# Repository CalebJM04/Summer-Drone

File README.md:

# Summer-Drone
Summer Drone project

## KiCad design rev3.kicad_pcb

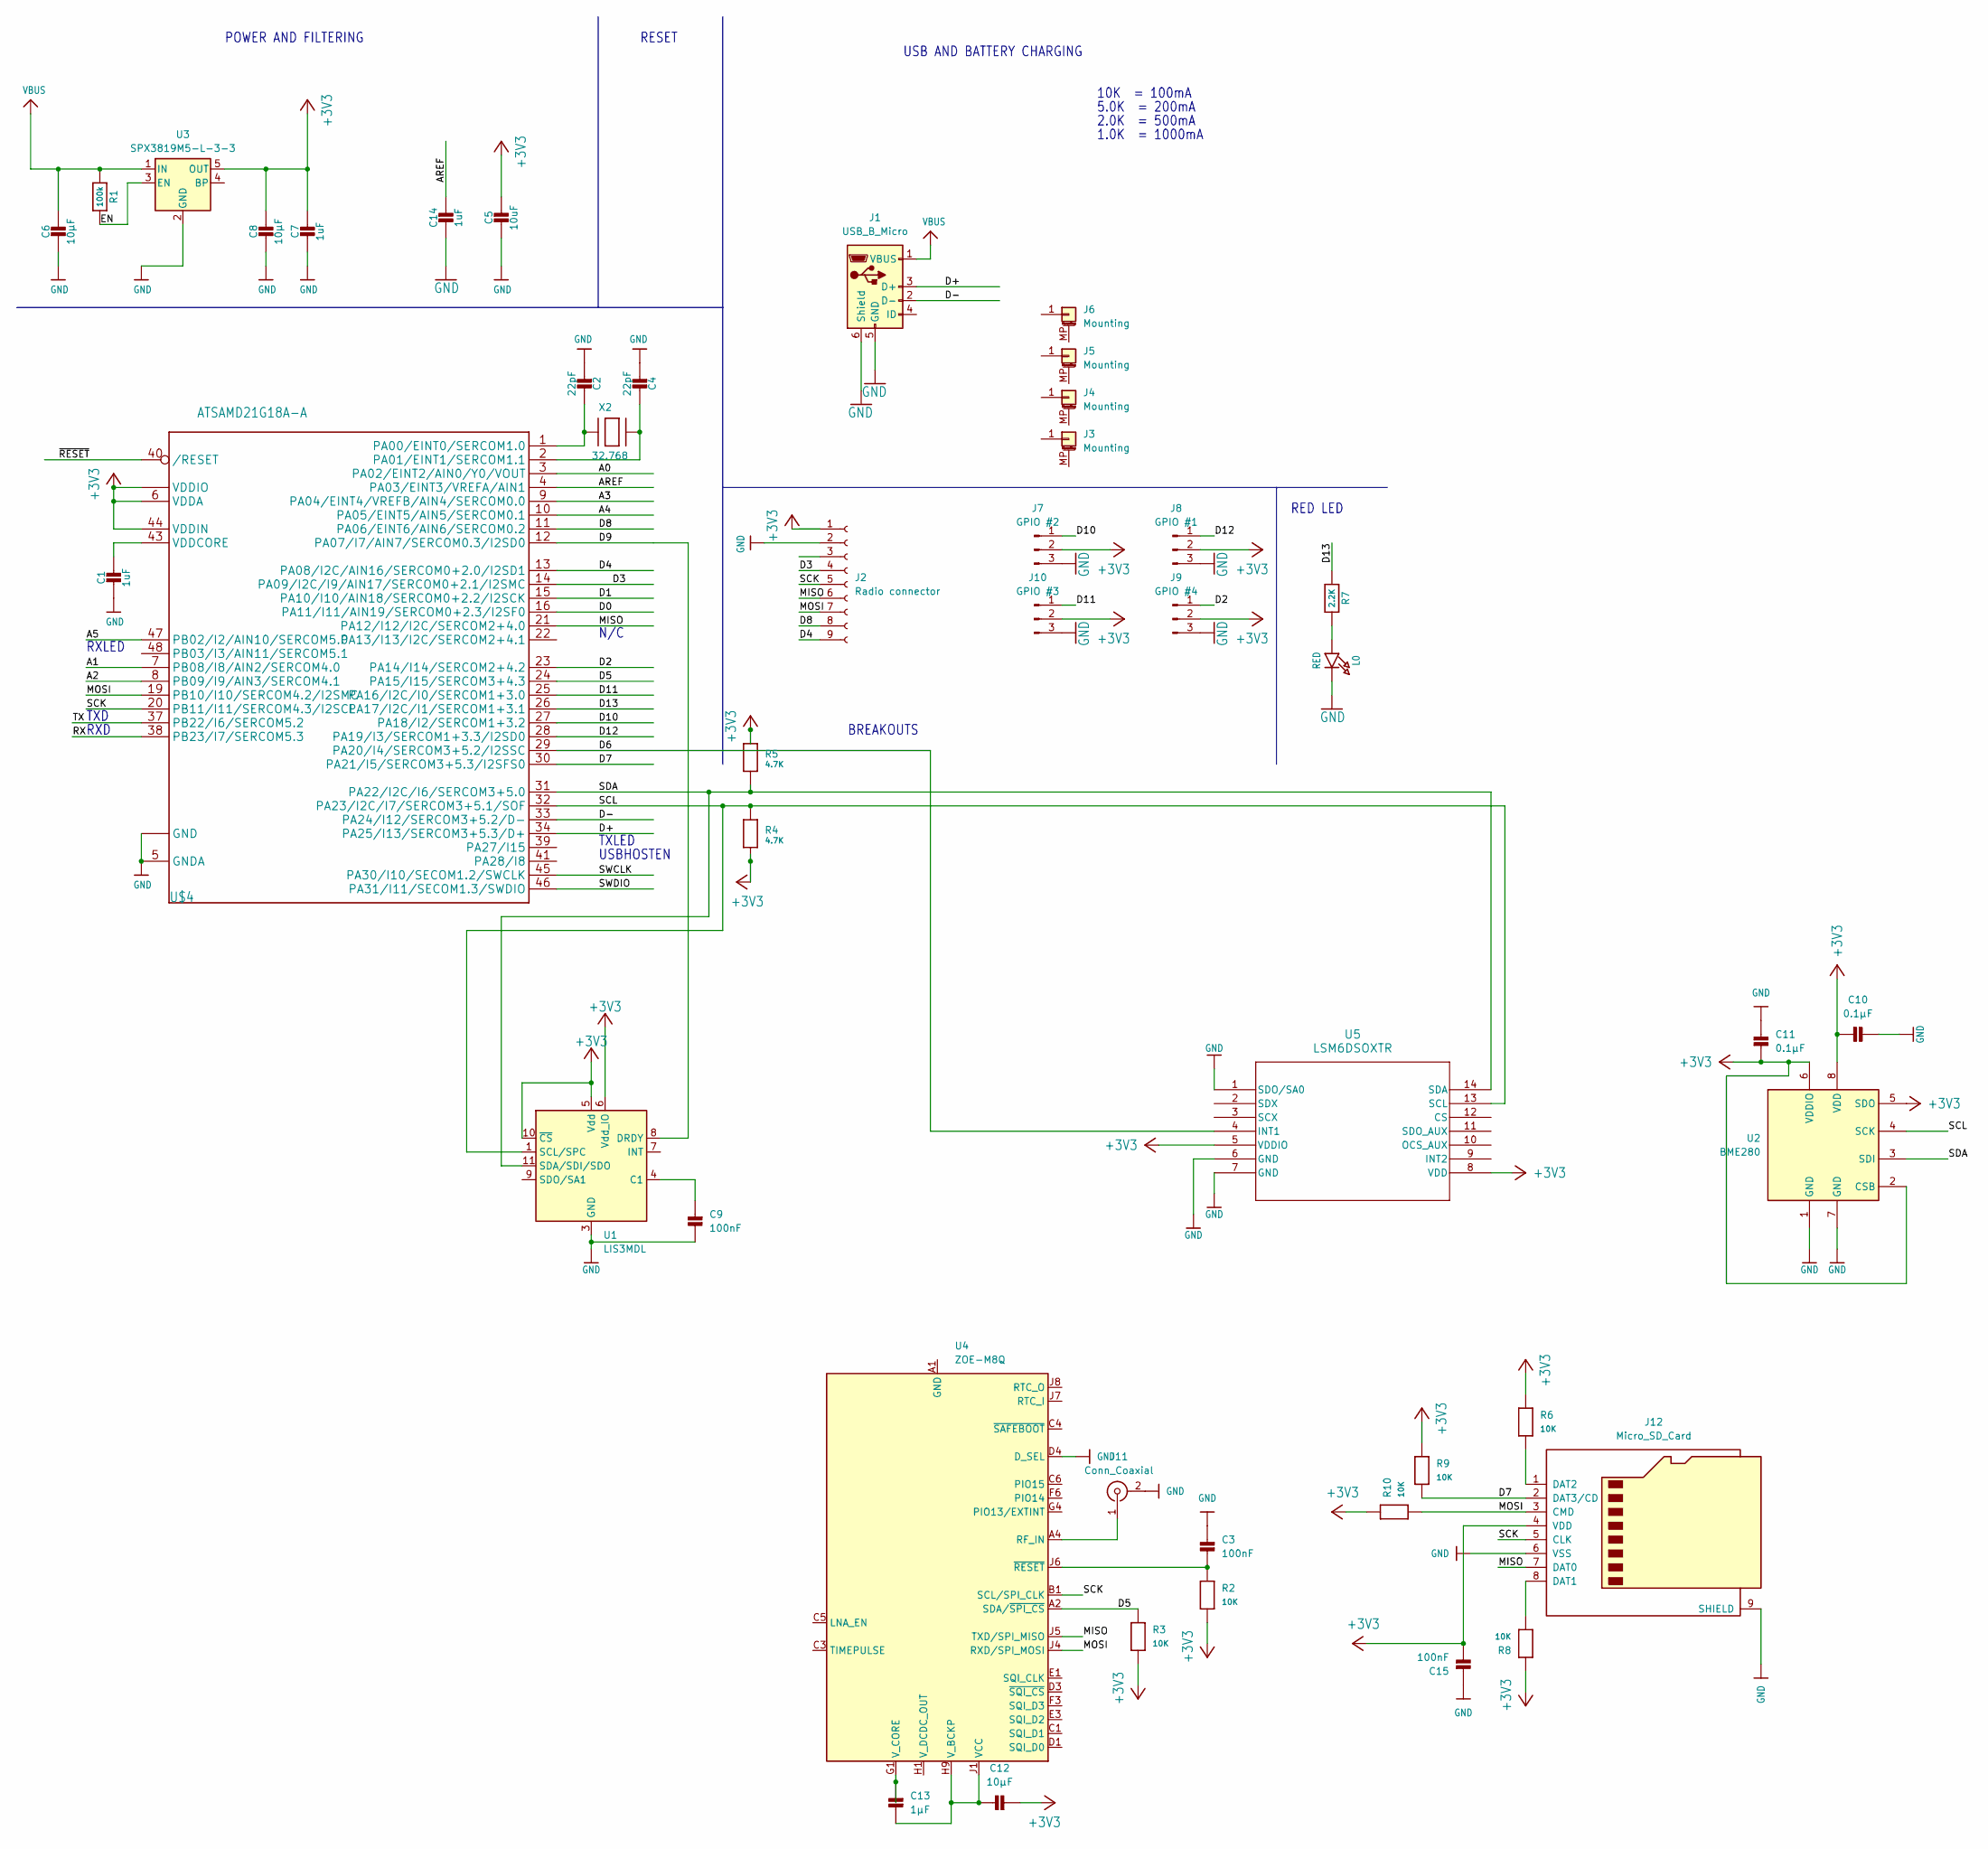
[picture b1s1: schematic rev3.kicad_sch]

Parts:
C1, C7, C14: 1uF; C_0805_2012Metric
C2, C4: 22pF; C_0805_2012Metric
C3, C9, C15: 100nF; C_0805_2012Metric
C5: 10uF; C_0805_2012Metric
C6, C8, C12: 10µF; C_0805_2012Metric
C10, C11: 0.1µF; C_0805_2012Metric
C13: 1µF; C_0805_2012Metric
J1: USB_B_Micro; USB_Micro-B_Molex-105017-0001
J2: Radio connector; PinSocket_1x09_P2.54mm_Vertical
J3, J4, J5, J6: Mounting; MountingHole_2.2mm_M2
J7: GPIO #2; PinHeader_1x04_P2.54mm_Vertical
J8: GPIO #1; PinHeader_1x04_P2.54mm_Vertical
J9: GPIO #4; PinHeader_1x04_P2.54mm_Vertical
J10: GPIO #3; PinHeader_1x04_P2.54mm_Vertical
J11: Conn_Coaxial; U.FL_Molex_MCRF_73412-0110_Vertical
J12: Micro_SD_Card; microSD_HC_Hirose_DM3AT-SF-PEJM5
L0: RED; LED_0805_2012Metric
R1: 100k; R_0201_0603Metric
R2, R3, R6, R8, R9, R10: 10K; R_0201_0603Metric
R4, R5: 4.7K; R_0201_0603Metric
R7: 2.2K; R_0201_0603Metric
U1: LIS3MDL; LGA-12_2x2mm_P0.5mm
U2: BME280; Bosch_LGA-8_2.5x2.5mm_P0.65mm_ClockwisePinNumbering
U3: SPX3819M5-L-3-3; SOT-23-5
U4: ZOE-M8Q; ublox_ZOE_M8
U5: LSM6DSOXTR; LGA-14L_STM
U$4: ATSAMD21G18A-A; TQFP-48_7x7mm_P0.5mm
X2: 32.768; Crystal_SMD_3215-2Pin_3.2x1.5mm

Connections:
+3V3: C5.1, C7.1, C8.1, C10.2, C11.2, C12.2, C15.1, J2.1, J7.2, J8.2, J9.2, J10.2, J12.4 (VDD), R2.1, R3.1, R4.1, R5.2, R6.2, R8.2, R9.2, R10.2, U1.5 (Vdd), U1.6 (Vdd_IO), U1.10 (~CS), U2.2 (CSB), U2.5 (SDO), U2.6 (VDDIO), U2.8 (VDD), U3.5 (OUT), U5.5 (VDDIO), U5.8 (VDD), U$4.6 (VDDA), U$4.17 (VDDIO), U$4.36 (VDDIO), U$4.44 (VDDIN)
/A0: U$4.3 (PA02/EINT2/AIN0/Y0/VOUT)
/A1: U$4.7 (PB08/I8/AIN2/SERCOM4.0)
/A2: U$4.8 (PB09/I9/AIN3/SERCOM4.1)
/A3: U$4.9 (PA04/EINT4/VREFB/AIN4/SERCOM0.0)
/A4: U$4.10 (PA05/EINT5/AIN5/SERCOM0.1)
/A5: U$4.47 (PB02/I2/AIN10/SERCOM5.0)
/AREF: C14.1, U$4.4 (PA03/EINT3/VREFA/AIN1)
/D0: U$4.16 (PA11/I11/AIN19/SERCOM0+2.3/I2SF0)
/D1: U$4.15 (PA10/I10/AIN18/SERCOM0+2.2/I2SCK)
/D2: J9.1, U$4.23 (PA14/I14/SERCOM2+4.2)
/D3: J2.4, U$4.14 (PA09/I2C/I9/AIN17/SERCOM0+2.1/I2SMC)
/D4: J2.9, U$4.13 (PA08/I2C/AIN16/SERCOM0+2.0/I2SD1)
/D5: R3.2, U4.A2 (SDA/~SPI_CS), U$4.24 (PA15/I15/SERCOM3+4.3)
/D6: U5.4 (INT1), U$4.29 (PA20/I4/SERCOM3+5.2/I2SSC)
/D7: J12.2 (DAT3/CD), R9.1, U$4.30 (PA21/I5/SERCOM3+5.3/I2SFS0)
/D8: J2.8, U$4.11 (PA06/EINT6/AIN6/SERCOM0.2)
/D9: U1.8 (DRDY), U$4.12 (PA07/I7/AIN7/SERCOM0.3/I2SD0)
/D10: J7.1, U$4.27 (PA18/I2/SERCOM1+3.2)
/D11: J10.1, U$4.25 (PA16/I2C/I0/SERCOM1+3.0)
/D12: J8.1, U$4.28 (PA19/I3/SERCOM1+3.3/I2SD0)
/D13: R7.1, U$4.26 (PA17/I2C/I1/SERCOM1+3.1)
/D+: J1.3 (D+), U$4.34 (PA25/I13/SERCOM3+5.3/D+)
/D-: J1.2 (D-), U$4.33 (PA24/I12/SERCOM3+5.2/D-)
/EN: R1.2, U3.3 (EN)
/MISO: J2.6, J12.7 (DAT0), U4.J5 (TXD/SPI_MISO), U$4.21 (PA12/I12/I2C/SERCOM2+4.0)
/MOSI: J2.7, J12.3 (CMD), R10.1, U4.J4 (RXD/SPI_MOSI), U$4.19 (PB10/I10/SERCOM4.2/I2SMC)
/RX: U$4.38 (PB23/I7/SERCOM5.3)
/SCK: J2.5, J12.5 (CLK), U4.B1 (SCL/SPI_CLK), U$4.20 (PB11/I11/SERCOM4.3/I2SCL)
/SCL: R4.2, U1.1 (SCL/SPC), U2.4 (SCK), U5.13 (SCL), U$4.32 (PA23/I2C/I7/SERCOM3+5.1/SOF)
/SDA: R5.1, U1.11 (SDA/SDI/SDO), U2.3 (SDI), U5.14 (SDA), U$4.31 (PA22/I2C/I6/SERCOM3+5.0)
/SWCLK: U$4.45 (PA30/I10/SECOM1.2/SWCLK)
/SWDIO: U$4.46 (PA31/I11/SECOM1.3/SWDIO)
/TX: U$4.37 (PB22/I6/SERCOM5.2)
/~RESET: U$4.40 (/RESET)
GND: C1.2, C2.2, C3.2, C4.2, C5.2, C6.2, C7.2, C8.2, C9.1, C10.1, C11.1, C14.2, C15.2, J1.5 (GND), J1.6 (Shield), J2.2, J7.3, J8.3, J9.3, J10.3, J11.2 (Ext), J12.6 (VSS), J12.9 (SHIELD), L0.2, U1.2 (GND), U1.3 (GND), U1.12 (GND), U2.1 (GND), U2.7 (GND), U3.2 (GND), U4.D4 (D_SEL), U5.1 (SDO/SA0), U5.6 (GND), U5.7 (GND), U$4.5 (GNDA), U$4.18 (GND), U$4.35 (GND), U$4.42 (GND), U$4.THERMAL (GND)
unnamed: J11.1 (In), U4.A4 (RF_IN)
unnamed: J12.8 (DAT1), R8.1
unnamed: J12.1 (DAT2), R6.1
unnamed: L0.1, R7.2
unnamed: C9.2, U1.4 (C1)
unnamed: U4.A1 (GND), U4.A3 (GND), U4.A5 (GND), U4.A7 (GND), U4.A8 (GND), U4.A9 (GND), U4.B9 (GND), U4.C7 (GND), U4.C9 (GND), U4.D6 (GND), U4.D9 (GND), U4.E7 (GND), U4.F7 (GND), U4.G3 (GND), U4.G6 (GND), U4.G7 (GND), U4.J3 (GND), U4.J9 (GND)
unnamed: C12.1, C13.1, U4.H9 (V_BCKP), U4.J1 (VCC), U4.J2 (VCC)
unnamed: C13.2, U4.G1 (V_CORE)
unnamed: C3.1, R2.2, U4.J6 (~RESET)
unnamed: C2.1, U$4.1 (PA00/EINT0/SERCOM1.0), X2.1
unnamed: C4.1, U$4.2 (PA01/EINT1/SERCOM1.1), X2.2
unnamed: C1.1, U$4.43 (VDDCORE)
VBUS: C6.1, J1.1 (VBUS), R1.1, U3.1 (IN)

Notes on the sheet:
POWER AND FILTERING
RED LED
2.0K = 500mA
10K = 100mA
5.0K = 200mA
N/C
USB AND BATTERY CHARGING
RXD
RESET
USBHOSTEN
RXLED
1.0K = 1000mA
TXLED
TXD
BREAKOUTS

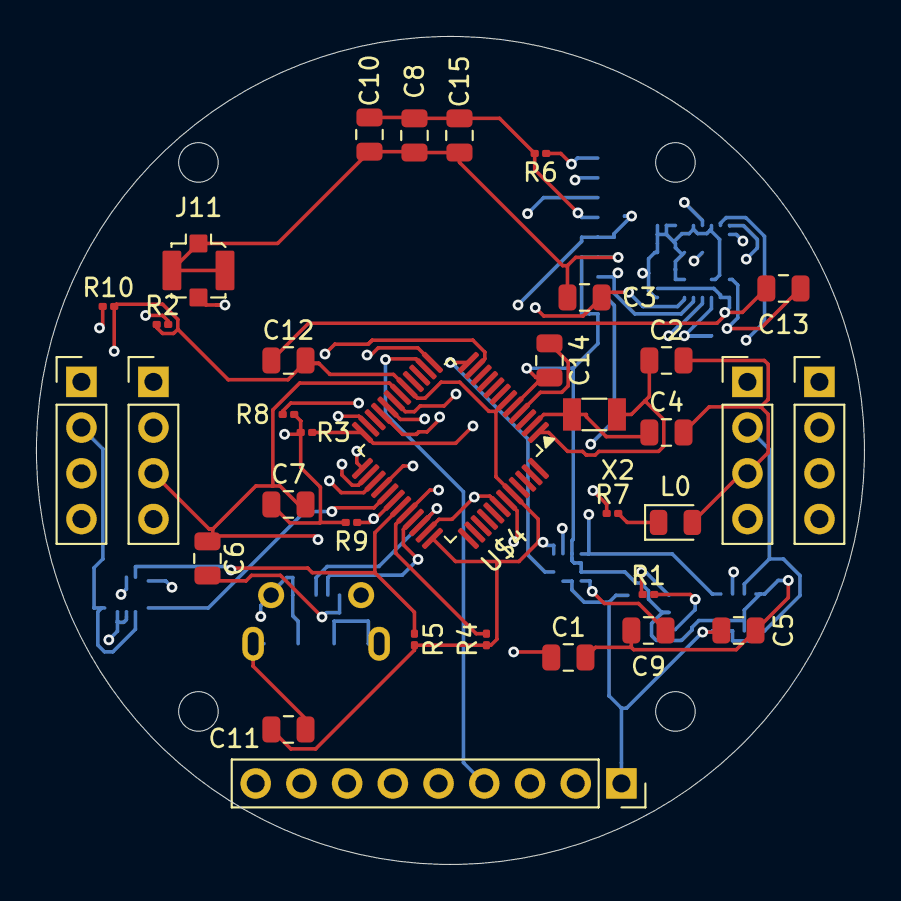
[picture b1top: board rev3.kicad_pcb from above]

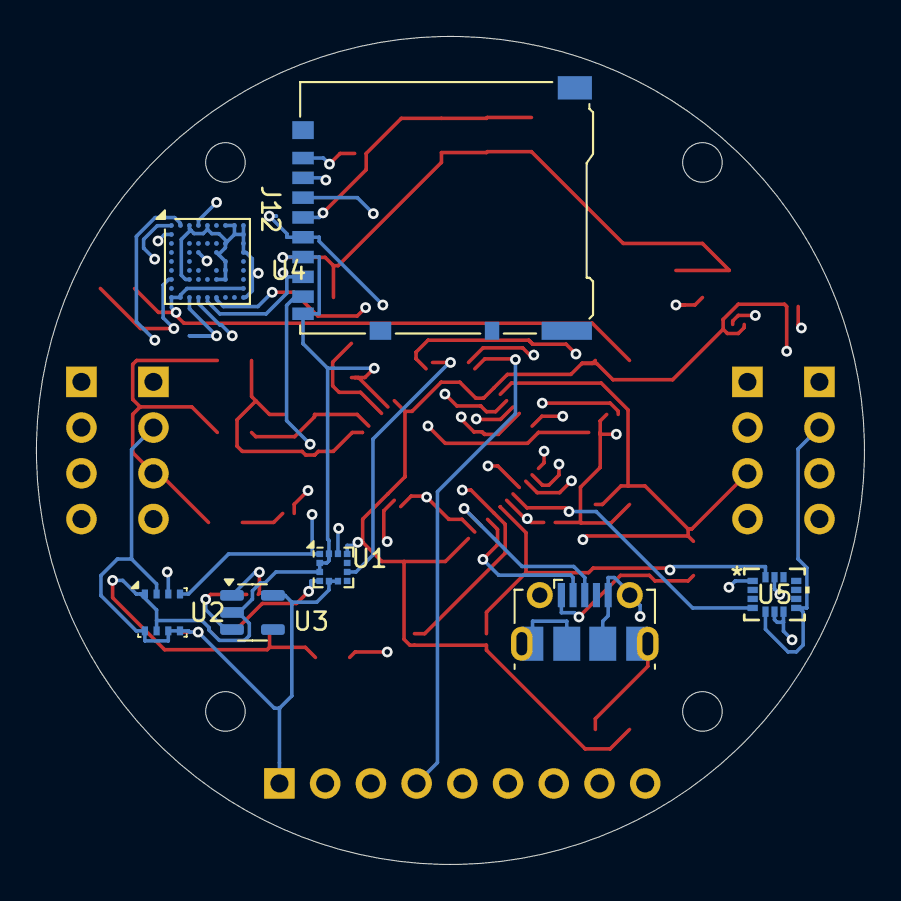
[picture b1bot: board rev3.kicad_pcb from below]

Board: 4 copper layers, 46.0 x 46.0 mm, 45 parts (7 on the bottom side), 36 nets.

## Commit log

2025-06-12 Starpath_v2 initial file
